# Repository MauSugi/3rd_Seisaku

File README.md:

# Remote Smart Alarm

3E制作実習「遠隔で止める目覚まし時計」

alarm unit と button unit の二つに分かれています。

### 使用した部品

・ESP32-DevKitC-VE

・DFPlayer Mini

・Speaker

・switch

・7seg 4digit display

etc...

### ディレクトリ構成

```text
3rd_Seisaku/
├── 3rd_Seisaku_hardware/        # ハードウェア関連
│   ├── 3rd_Seisaku_3Ddata       # GitHub上でプレビュー可能なstlファイル
│   ├── 3rd_Seisaku_Circuit      # KiCadで作成した回路図及びpcbデータ(両unit共通)
│   └── 3rd_Seisaku_Enclosure    # Fusionで作成した筐体のcadデータ
└── 3rd_Seisaku_software/        # ソフトウェア関連
    ├── 3rd_Seisaku_alarm        # alarm unitのプログラム
    └── 3rd_Seisaku_button       # button unitのプログラム

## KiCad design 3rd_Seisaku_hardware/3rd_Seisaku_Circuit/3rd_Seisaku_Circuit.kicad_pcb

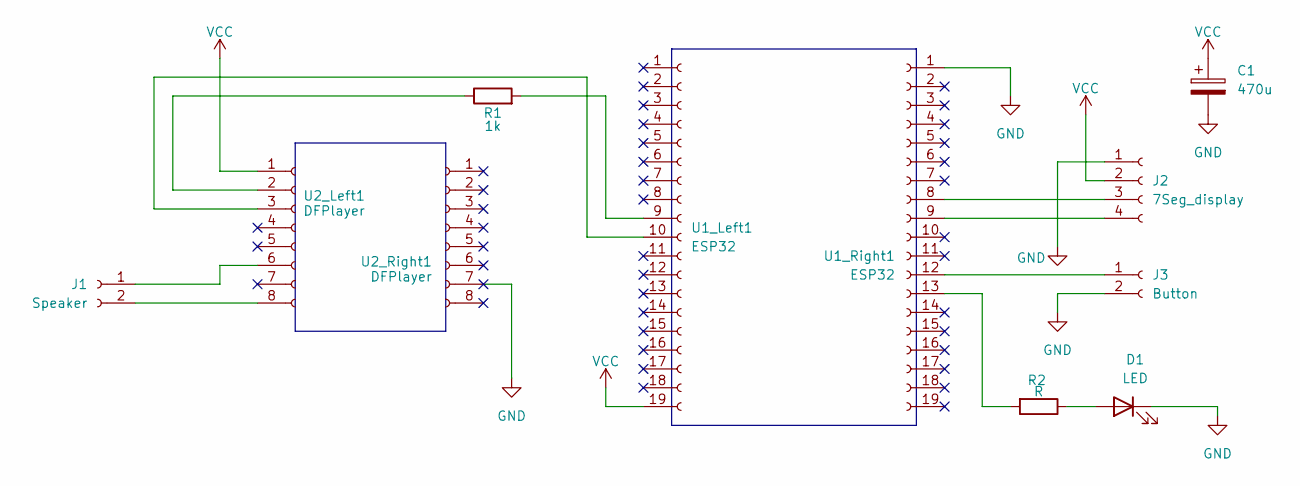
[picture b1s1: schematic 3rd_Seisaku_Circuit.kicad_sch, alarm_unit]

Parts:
C1: 470u; CP_Radial_D8.0mm_P3.50mm
D1: LED; LED_D5.0mm
J1: Speaker; JST_XH_B2B-XH-A_1x02_P2.50mm_Vertical
J2: 7Seg_display; JST_PH_B4B-PH-K_1x04_P2.00mm_Vertical
J3: Button; JST_XH_B2B-XH-A_1x02_P2.50mm_Vertical
R1: 1k; R_Axial_DIN0207_L6.3mm_D2.5mm_P7.62mm_Horizontal
R2: R; R_Axial_DIN0207_L6.3mm_D2.5mm_P7.62mm_Horizontal
U1_Left1, U1_Right1: ESP32; PinSocket_1x19_P2.54mm_Vertical
U2_Left1, U2_Right1: DFPlayer; PinSocket_1x08_P2.54mm_Vertical

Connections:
GND: C1.2, D1.1 (K), J2.1, J3.2, U1_Right1.1, U2_Right1.7 (GND)
unnamed: D1.2 (A), R2.1
unnamed: J1.1, U2_Left1.6 (SPK1)
unnamed: J1.2, U2_Left1.8 (SPK2)
unnamed: J2.3, U1_Right1.8
unnamed: J2.4, U1_Right1.9
unnamed: J3.1, U1_Right1.12
unnamed: R1.2, U1_Left1.9
unnamed: U1_Left1.10, U2_Left1.3 (TX)
unnamed: R2.2, U1_Right1.13
unnamed: R1.1, U2_Left1.2 (RX)
VCC: C1.1, J2.2, U1_Left1.19, U2_Left1.1 (VCC)

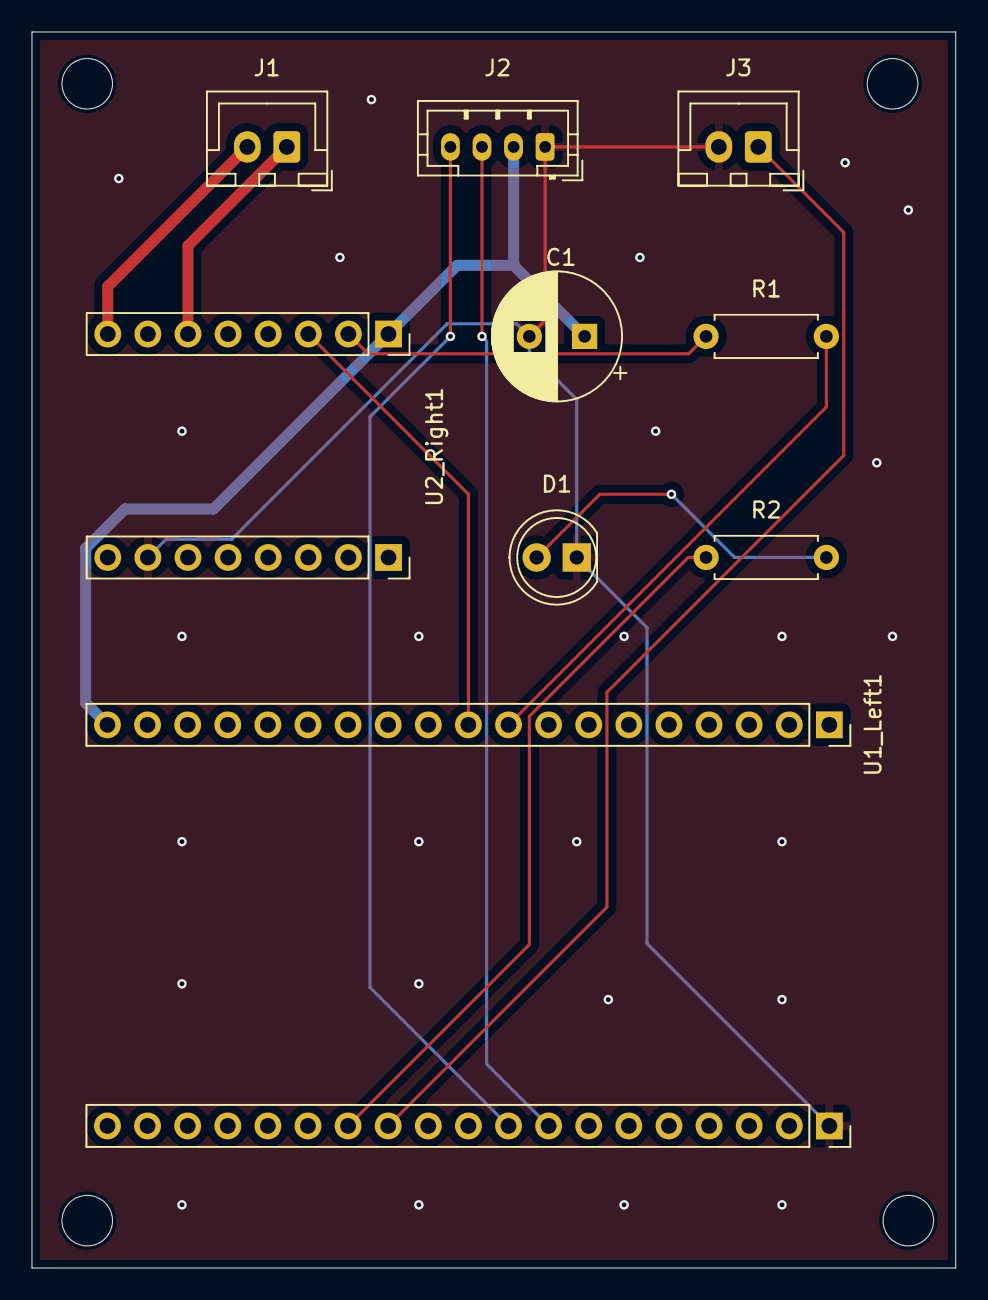
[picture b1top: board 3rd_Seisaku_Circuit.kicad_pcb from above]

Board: 2 copper layers, 58.5 x 78.3 mm, 11 parts (0 on the bottom side), 12 nets.

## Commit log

2026-01-08 Add initial commits
2026-01-08 いったん
2026-01-15 動作確認した
2026-01-19 web改良して動作確認した
2026-01-19 ui変更&デバッグ用stop正常に動作！
2026-01-20 基板実装して、動作確認！
2026-01-21 一応、動作確認ok
2026-01-30 基板データ送信
2026-01-30 hardware&softwareファイル構成制作
2026-01-30 ファイル構成整理
2026-01-30 Create README.md with project directory structure
    Add initial structure and file descriptions for the project.
2026-01-30 Update project title and section headers in README
2026-01-30 Revise README
    Updated project title and added component list.
2026-01-30 Revise README
    Updated formatting and structure of the README file.
2026-01-30 Revise README
    Formatted the components list and added directory structure.
2026-02-01 プレゼン用変更
